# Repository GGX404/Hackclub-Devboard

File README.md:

# Hackclub-Devboard
My devboard project for Hackclub. Following the guide on the website.

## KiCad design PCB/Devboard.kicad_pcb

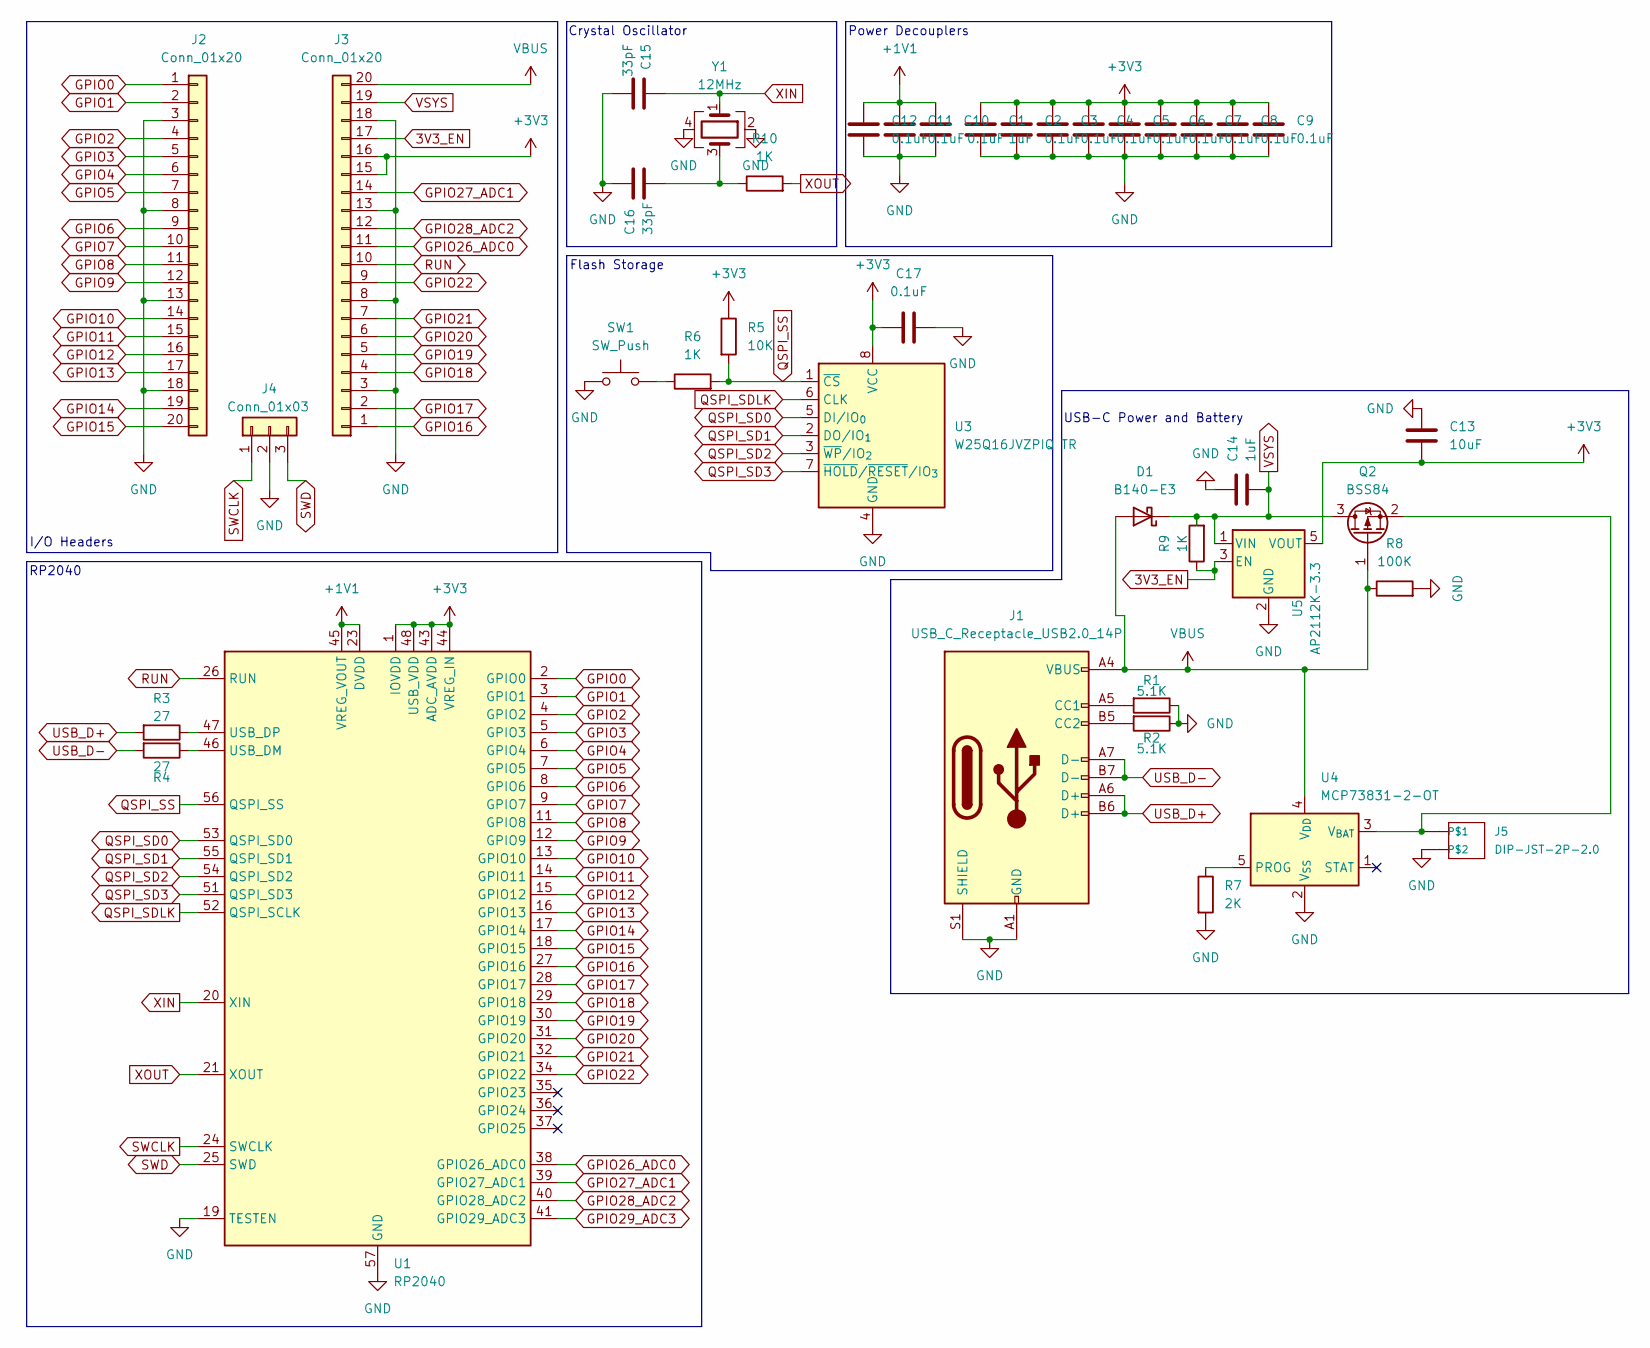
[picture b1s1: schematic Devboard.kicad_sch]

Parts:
C1, C14: 1uF; C_0402_1005Metric
C2, C3, C4, C5, C6, C7, C8, C9, C10, C11, C12, C17: 0.1uF; C_0402_1005Metric
C13: 10uF; C_0402_1005Metric
C15, C16: 33pF; C_0402_1005Metric
D1: B140-E3; D_SMA
J1: USB_C_Receptacle_USB2.0_14P; USB_C_Receptacle_HRO_TYPE-C-31-M-12
J2, J3: Conn_01x20; PinHeader_1x20_P2.54mm_Vertical
J4: Conn_01x03; PinHeader_1x03_P2.54mm_Vertical
J5: DIP-JST-2P-2.0; JST_PH_B2B-PH-K_1x02_P2.00mm_Vertical
Q2: BSS84; SOT-23
R1, R2: 5.1K; C_0402_1005Metric
R3, R4: 27; C_0402_1005Metric
R5: 10K; C_0402_1005Metric
R6, R9, R10: 1K; C_0402_1005Metric
R7: 2K; C_0402_1005Metric
R8: 100K; C_0402_1005Metric
SW1: SW_Push; SW_Push_SPST_NO_Alps_SKRK
U1: RP2040; QFN-56-1EP_7x7mm_P0.4mm_EP3.2x3.2mm
U3: W25Q16JVZPIQ TR; Winbond_USON-8-1EP_3x2mm_P0.5mm_EP0.2x1.6mm
U4: MCP73831-2-OT; SOT-23-5
U5: AP2112K-3.3; SOT-23-5
Y1: 12MHz; Crystal_SMD_3225-4Pin_3.2x2.5mm

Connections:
3V3_EN: J3.17, R9.1, U5.3 (EN)
+1V1: C10.1, C11.1, C12.1, U1.23 (DVDD), U1.45 (VREG_VOUT), U1.50 (DVDD)
+3V3: C1.1, C2.1, C3.1, C4.1, C5.1, C6.1, C7.1, C8.1, C9.1, C13.2, C17.1, J3.15, J3.16, R5.1, U1.1 (IOVDD), U1.10 (IOVDD), U1.22 (IOVDD), U1.33 (IOVDD), U1.42 (IOVDD), U1.43 (ADC_AVDD), U1.44 (VREG_IN), U1.48 (USB_VDD), U1.49 (IOVDD), U3.8 (VCC), U5.5 (VOUT)
GND: C1.2, C2.2, C3.2, C4.2, C5.2, C6.2, C7.2, C8.2, C9.2, C10.2, C11.2, C12.2, C13.1, C14.1, C15.2, C16.1, C17.2, J1.A1 (GND), J1.A12 (GND), J1.B1 (GND), J1.B12 (GND), J1.S1 (SHIELD), J2.3, J2.8, J2.13, J2.18, J3.3, J3.8, J3.13, J3.18, J4.2, J5.2, R1.1, R2.1, R7.2, R8.2, SW1.1, U1.19 (TESTEN), U1.57 (GND), U3.4 (GND), U4.2 (V_{SS}), U5.2 (GND), Y1.2, Y1.4
GPIO0: J2.1, U1.2 (GPIO0)
GPIO1: J2.2, U1.3 (GPIO1)
GPIO2: J2.4, U1.4 (GPIO2)
GPIO3: J2.5, U1.5 (GPIO3)
GPIO4: J2.6, U1.6 (GPIO4)
GPIO5: J2.7, U1.7 (GPIO5)
GPIO6: J2.9, U1.8 (GPIO6)
GPIO7: J2.10, U1.9 (GPIO7)
GPIO8: J2.11, U1.11 (GPIO8)
GPIO9: J2.12, U1.12 (GPIO9)
GPIO10: J2.14, U1.13 (GPIO10)
GPIO11: J2.15, U1.14 (GPIO11)
GPIO12: J2.16, U1.15 (GPIO12)
GPIO13: J2.17, U1.16 (GPIO13)
GPIO14: J2.19, U1.17 (GPIO14)
GPIO15: J2.20, U1.18 (GPIO15)
GPIO16: J3.1, U1.27 (GPIO16)
GPIO17: J3.2, U1.28 (GPIO17)
GPIO18: J3.4, U1.29 (GPIO18)
GPIO19: J3.5, U1.30 (GPIO19)
GPIO20: J3.6, U1.31 (GPIO20)
GPIO21: J3.7, U1.32 (GPIO21)
GPIO22: J3.9, U1.34 (GPIO22)
GPIO26_ADC0: J3.11, U1.38 (GPIO26_ADC0)
GPIO27_ADC1: J3.14, U1.39 (GPIO27_ADC1)
GPIO28_ADC2: J3.12, U1.40 (GPIO28_ADC2)
GPIO29_ADC3: U1.41 (GPIO29_ADC3)
unnamed: C16.2, R10.1, Y1.3
unnamed: J1.A5 (CC1), R1.2
unnamed: J1.B5 (CC2), R2.2
unnamed: J5.1, Q2.2 (S), U4.3 (V_{BAT})
unnamed: R6.1, SW1.2
unnamed: R4.1, U1.46 (USB_DM)
unnamed: R3.1, U1.47 (USB_DP)
unnamed: R7.1, U4.5 (PROG)
QSPI_SD0: U1.53 (QSPI_SD0), U3.5 (DI/IO_{0})
QSPI_SD1: U1.55 (QSPI_SD1), U3.2 (DO/IO_{1})
QSPI_SD2: U1.54 (QSPI_SD2), U3.3 (~WP/IO_{2})
QSPI_SD3: U1.51 (QSPI_SD3), U3.7 (~HOLD/~RESET/IO_{3})
QSPI_SDLK: U1.52 (QSPI_SCLK), U3.6 (CLK)
QSPI_SS: R5.2, R6.2, U1.56 (QSPI_SS), U3.1 (~CS)
RUN: J3.10, U1.26 (RUN)
SWCLK: J4.1, U1.24 (SWCLK)
SWD: J4.3, U1.25 (SWD)
USB_D+: J1.A6 (D+), J1.B6 (D+), R3.2
USB_D-: J1.A7 (D-), J1.B7 (D-), R4.2
VBUS: D1.2 (A), J1.A4 (VBUS), J1.A9 (VBUS), J1.B4 (VBUS), J1.B9 (VBUS), J3.20, Q2.1 (G), R8.1, U4.4 (V_{DD})
VSYS: C14.2, D1.1 (K), J3.19, Q2.3 (D), R9.2, U5.1 (VIN)
XIN: C15.1, U1.20 (XIN), Y1.1
XOUT: R10.2, U1.21 (XOUT)

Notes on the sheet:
Power Decouplers
Flash Storage
Crystal Oscillator
USB-C Power and Battery
RP2040
I/O Headers

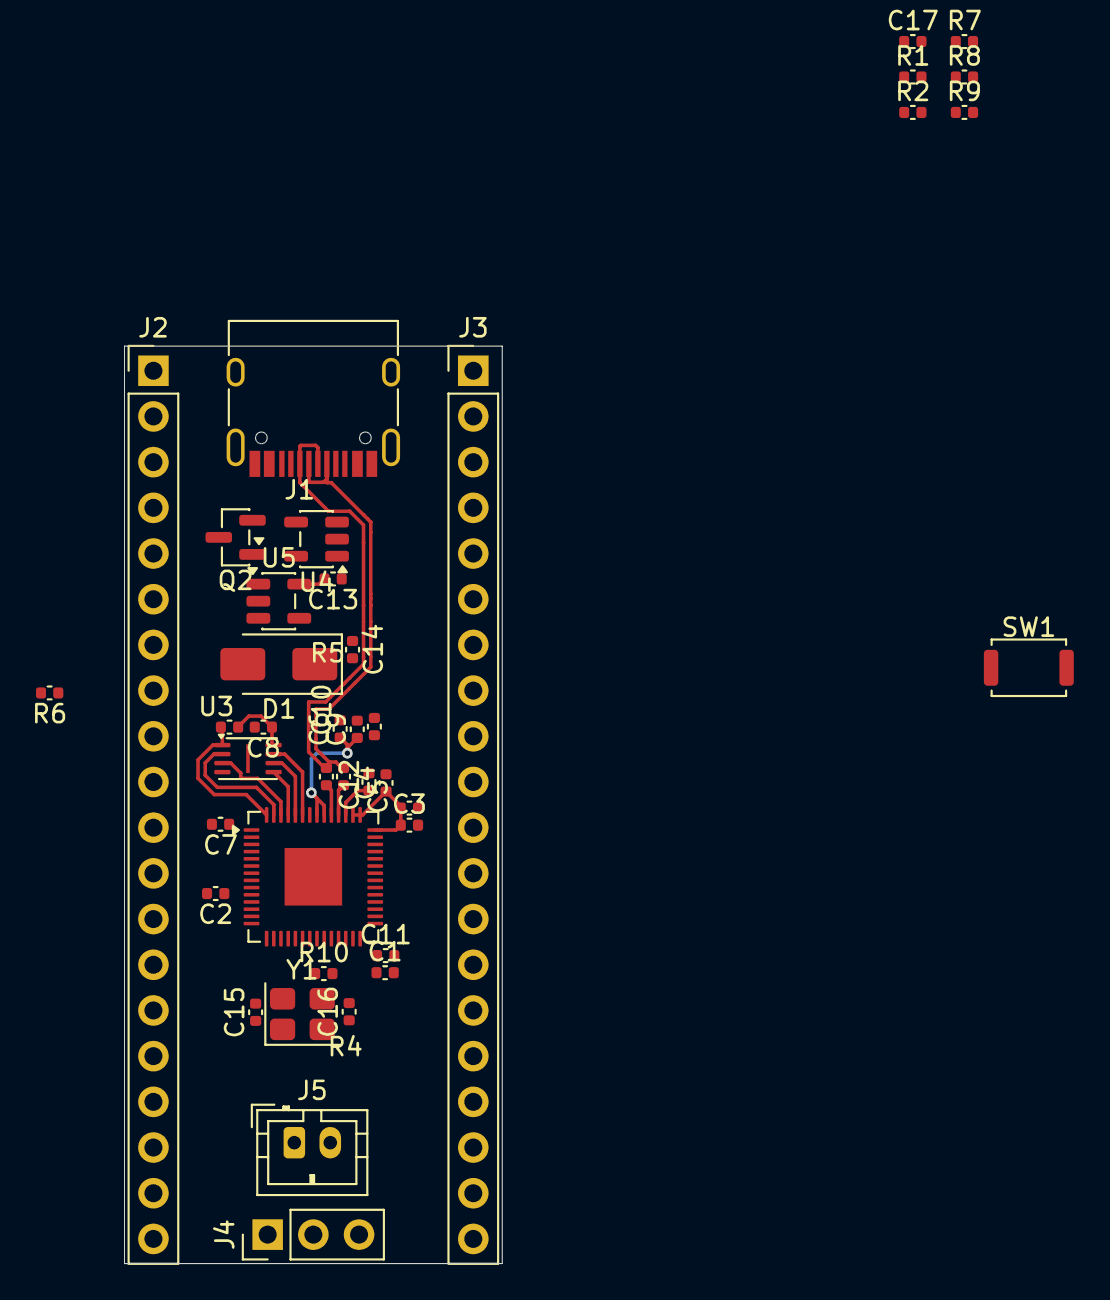
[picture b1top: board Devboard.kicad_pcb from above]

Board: 2 copper layers, 21.0 x 51.0 mm, 40 parts (0 on the bottom side), 53 nets.

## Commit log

2026-01-02 Added PCB folder
